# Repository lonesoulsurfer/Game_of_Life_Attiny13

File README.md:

# Game_of_Life_Attiny13

The Game of Life is a cellular automation created by mathamatician John Conway. It's what is known as a zero player game, meaning that its evolution and game play is determined by its initial state and requires no further input. You interact with the Game of Life by creating an initial configuration and observing how it evolves.

The game itself is based on a few, simple, mathematical rules consisting of a grid of cells that can either live, die or multiply. When the game is run, the cells can give the illusion (or are they alive...) that they are alive which is what makes this game so interesting.

There's plenty of information on the Internet about the Game of Life. If you are interested in learning more then definitely check out the links belowe which have some great resources and info.

This build is based on another Instructable by Sanuki Udon who created the code and project.

My contribution is; I created a PCB and front panel for the project and have tweaked some of the parameters in the sketch to make the game run faster and longer.  I also added a dufusser to the front of the LED's which I think gives more of a feeling that the cells are alive.

Youtube Vid
https://youtu.be/9KQFAfuK4dU

Instructables (Step by step guide on how to build your own
https://www.instructables.com/Conways-Game-of-Life-Running-on-an-ATtiny13/

Original Build on Instructables
https://www.instructables.com/Conways-Life-of-Life-of-1616-Cells-Made-With-ATtin/

Wikipedia
https://en.wikipedia.org/wiki/Conway%27s_Game_of_Life

Play Game of Life on line
https://playgameoflife.com/

Building a computer in the Game of Life
https://www.nicolasloizeau.com/gol-computer

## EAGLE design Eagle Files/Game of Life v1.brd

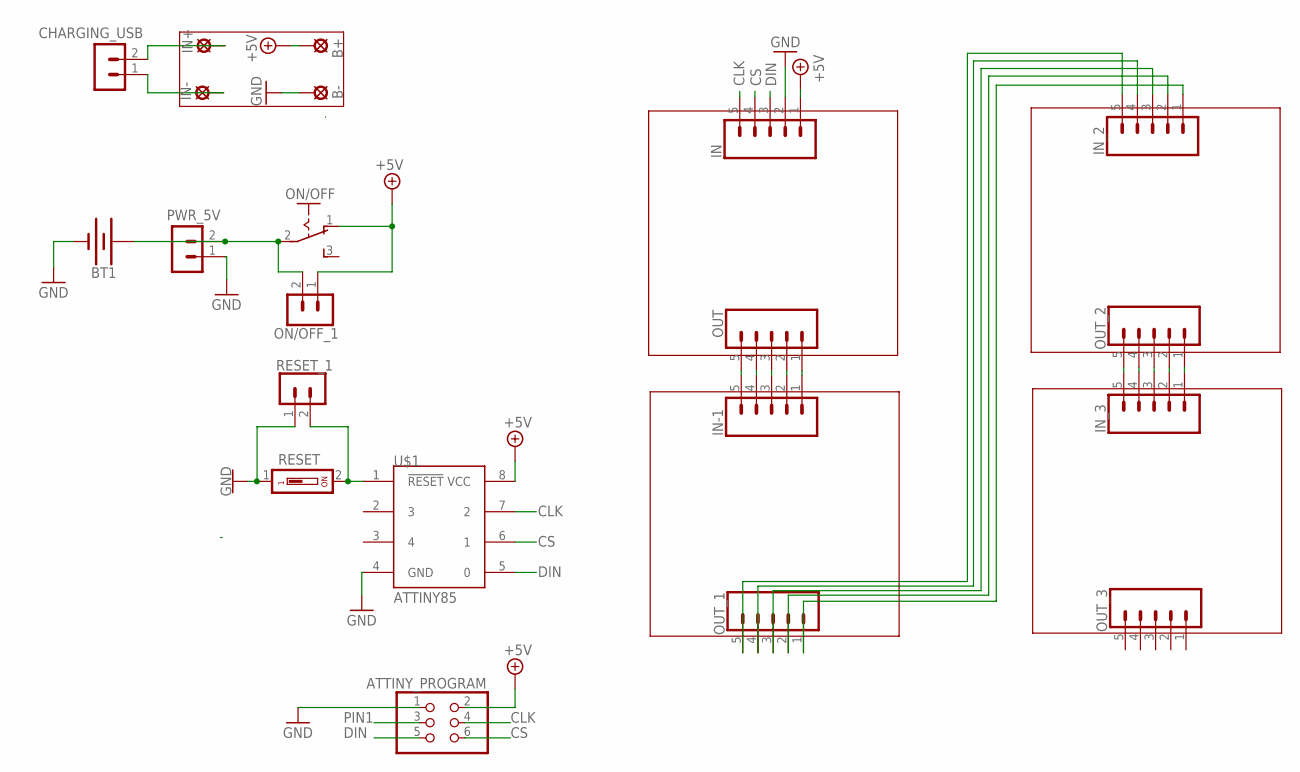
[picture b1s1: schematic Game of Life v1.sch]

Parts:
ATTINY_PROGRAM: PINHD-2X3; 2X03
B+: LSP11
B-: LSP11
BT1: BATTERY-18650; BATTERY_18650-HOLDER
CHARGING_USB: B2B-PH-K-S
IN: CONN_05; 1X05
IN+: LSP11
IN-: LSP11
IN-1: CONN_05; 1X05
IN_2, IN_3: CONN_05; 1X05
ON/OFF: M251
ON/OFF_1: B2B-PH-K-S
OUT: CONN_05; 1X05
OUT_1, OUT_2, OUT_3: CONN_05; 1X05
PWR_5V: B2B-PH-K-S
RESET: DS01; DS-01
RESET_1: B2B-PH-K-S
U$1: ATTINY85; 8P3

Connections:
+5V: ATTINY_PROGRAM.2, B+.MP, IN.1, ON/OFF.1 (O), ON/OFF_1.1, U$1.8 (VCC)
CLK: ATTINY_PROGRAM.4, IN.5, U$1.7 (2)
CS: ATTINY_PROGRAM.6, IN.4, U$1.6 (1)
DIN: ATTINY_PROGRAM.5, IN.3, U$1.5 (0)
GND: ATTINY_PROGRAM.1, B-.MP, BT1.GND@1 (-), IN.2, PWR_5V.1, RESET.1, RESET_1.1, U$1.4 (GND)
unnamed: BT1.PWR@1 (+), ON/OFF.2, ON/OFF_1.2, PWR_5V.2
unnamed: CHARGING_USB.2, IN+.MP
unnamed: IN-1.1, OUT.1
unnamed: IN-1.2, OUT.2
unnamed: IN-1.3, OUT.3
unnamed: IN-1.4, OUT.4
unnamed: IN-1.5, OUT.5
unnamed: IN_3.1, OUT_2.1
unnamed: IN_3.2, OUT_2.2
unnamed: IN_3.3, OUT_2.3
unnamed: IN_3.4, OUT_2.4
unnamed: IN_3.5, OUT_2.5
unnamed: IN_2.1, OUT_1.1
unnamed: IN_2.2, OUT_1.2
unnamed: IN_2.3, OUT_1.3
unnamed: IN_2.5, OUT_1.5
unnamed: IN_2.4, OUT_1.4
unnamed: CHARGING_USB.1, IN-.MP
PIN1: ATTINY_PROGRAM.3, RESET.2, RESET_1.2, U$1.1 (!RESET)

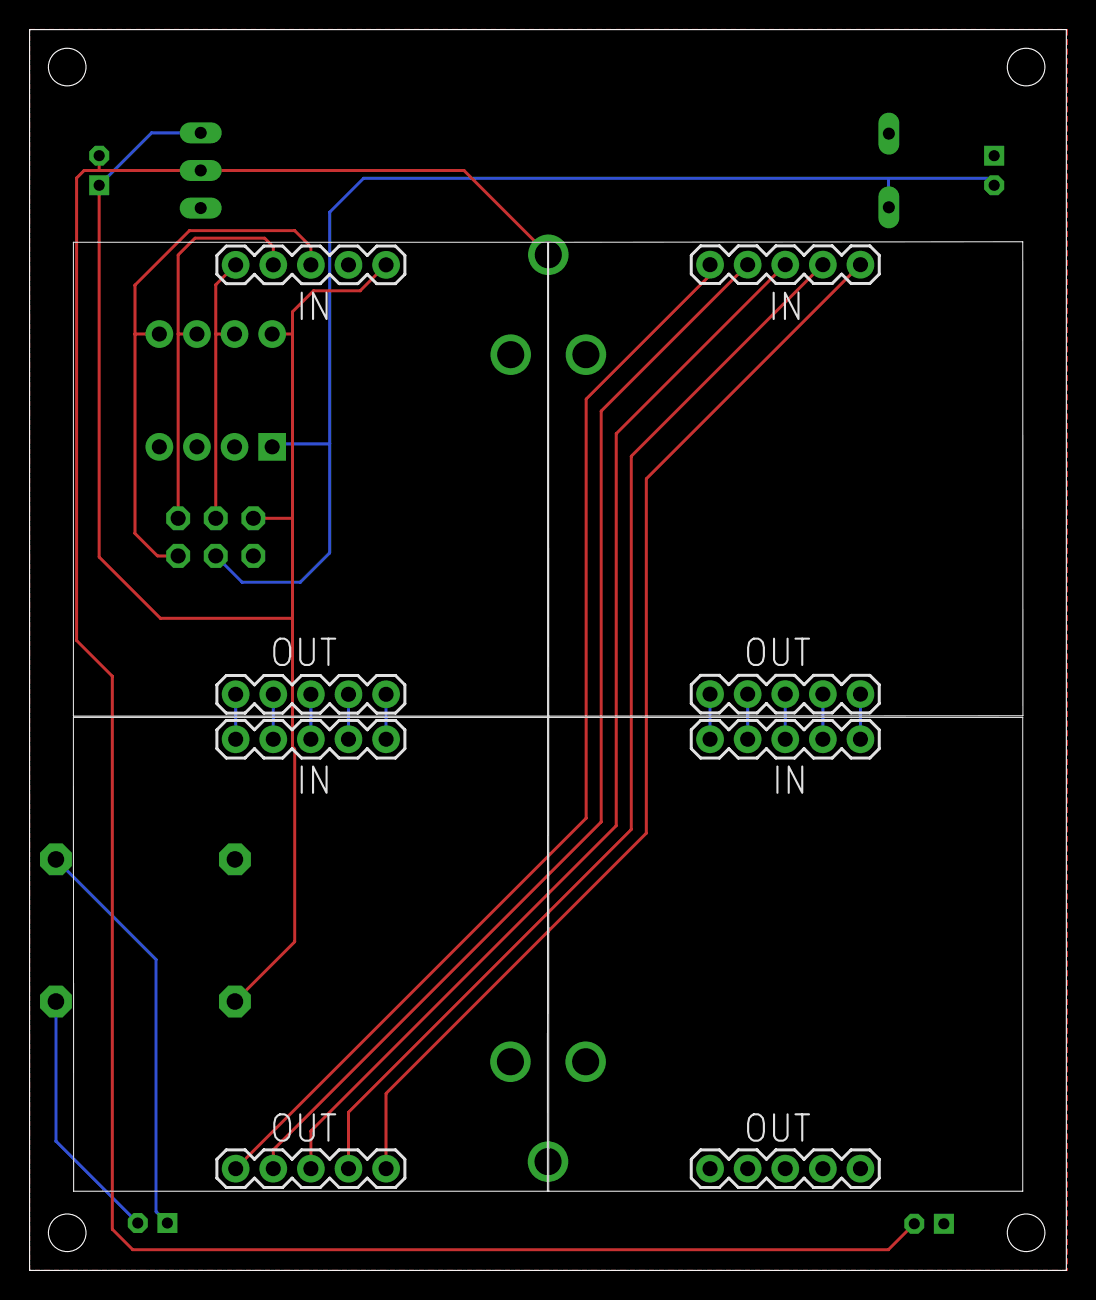
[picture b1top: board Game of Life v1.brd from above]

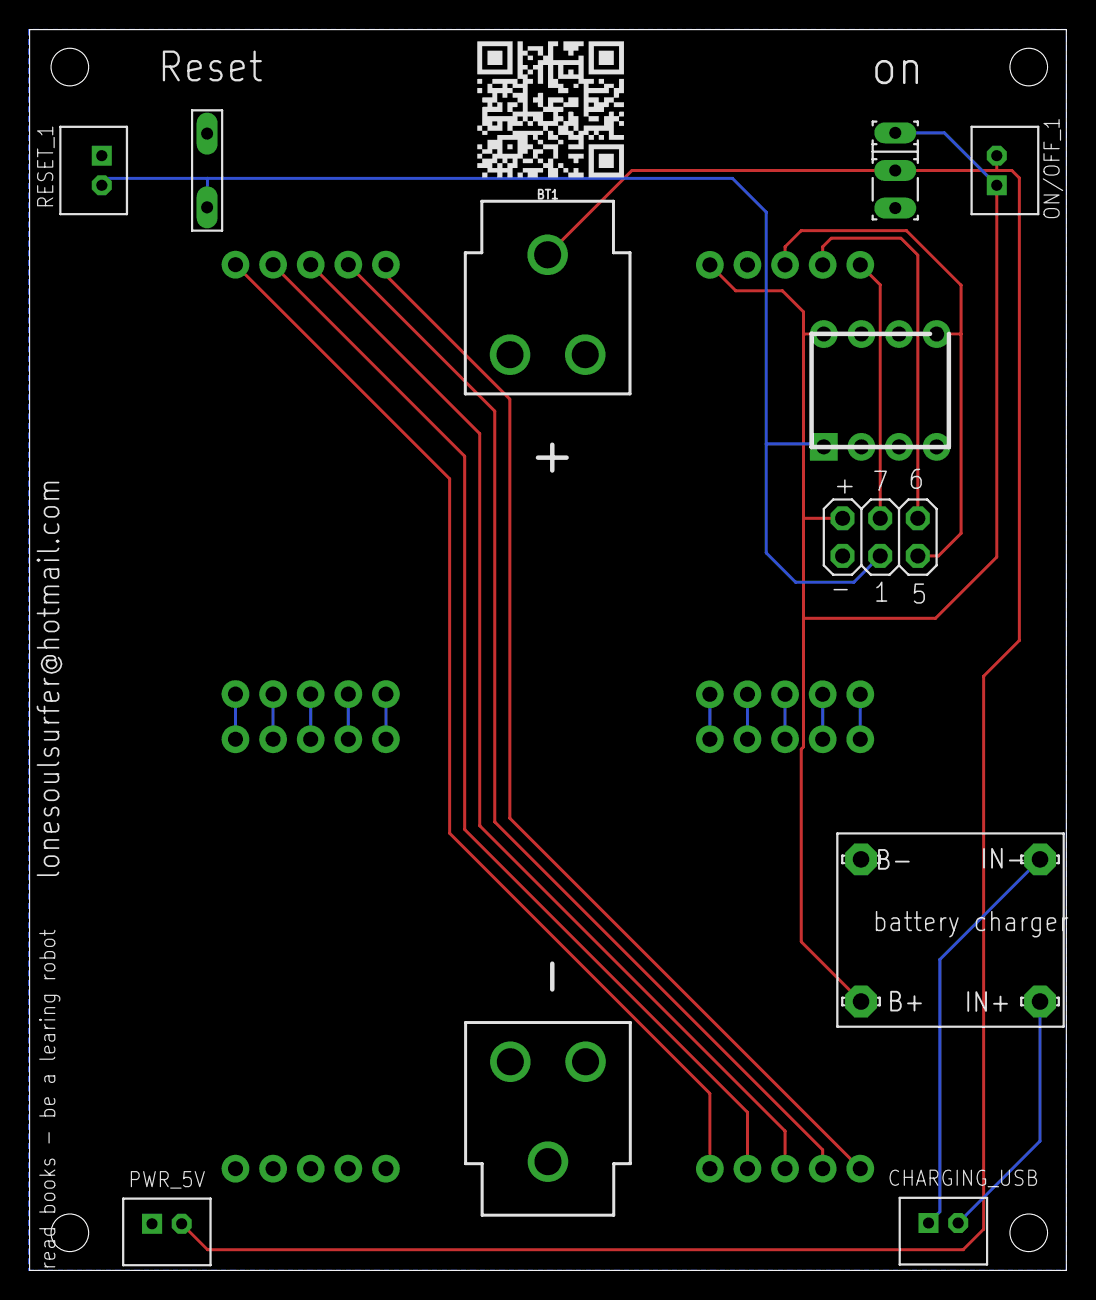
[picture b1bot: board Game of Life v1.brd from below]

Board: 2 copper layers, 70.0 x 83.8 mm, 21 parts (13 on the bottom side), 24 nets.

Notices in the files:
parts and their libraries:
SparkFun-Connectors: Licensing: Creative Commons ShareAlike 4.0 International - https://creativecommons.org/licenses/by-sa/4.0
